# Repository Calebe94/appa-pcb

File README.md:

# Appa keyboard - PCB

This keyboard is inspired by [Plaid](https://github.com/AntonioPelayo/plaid-through-hole-keyboard) and [Gherkin Apls 1.1](https://www.40percent.club/2017/08/gherkin-alps-11.html).

I'm using white APLS switches for this project and Arduino Pro Mini as the core microcontroller.

## Dependencies

* [Kicad 6+](https://packages.debian.org/bookworm/kicad).

## Symbols and Footprints

* I'm using an slightly modded version of [ARDUINO PRO MINI](https://www.snapeda.com/parts/Arduino%20Pro%20Mini/Arduino/view-part/?t=arduino+pro+mini&welcome=home) from [SnapEDA](https://www.snapeda.com). (I've just added a couple of pins at the bottom at the board because my PRO Mini uses the TQFP and QFN/MLF package of the ATMEGA328p);
* For the ALPS switches and the diodes I'm using the [keyboard_parts.pretty](https://github.com/tmk/keyboard_parts.pretty) footprints;
* As for the rest I'm using the KiCAD's stock footprints.

## Schematic

# License

All software is covered under [GNU General Public License v3.0](https://www.gnu.org/licenses/gpl-3.0.en.html).

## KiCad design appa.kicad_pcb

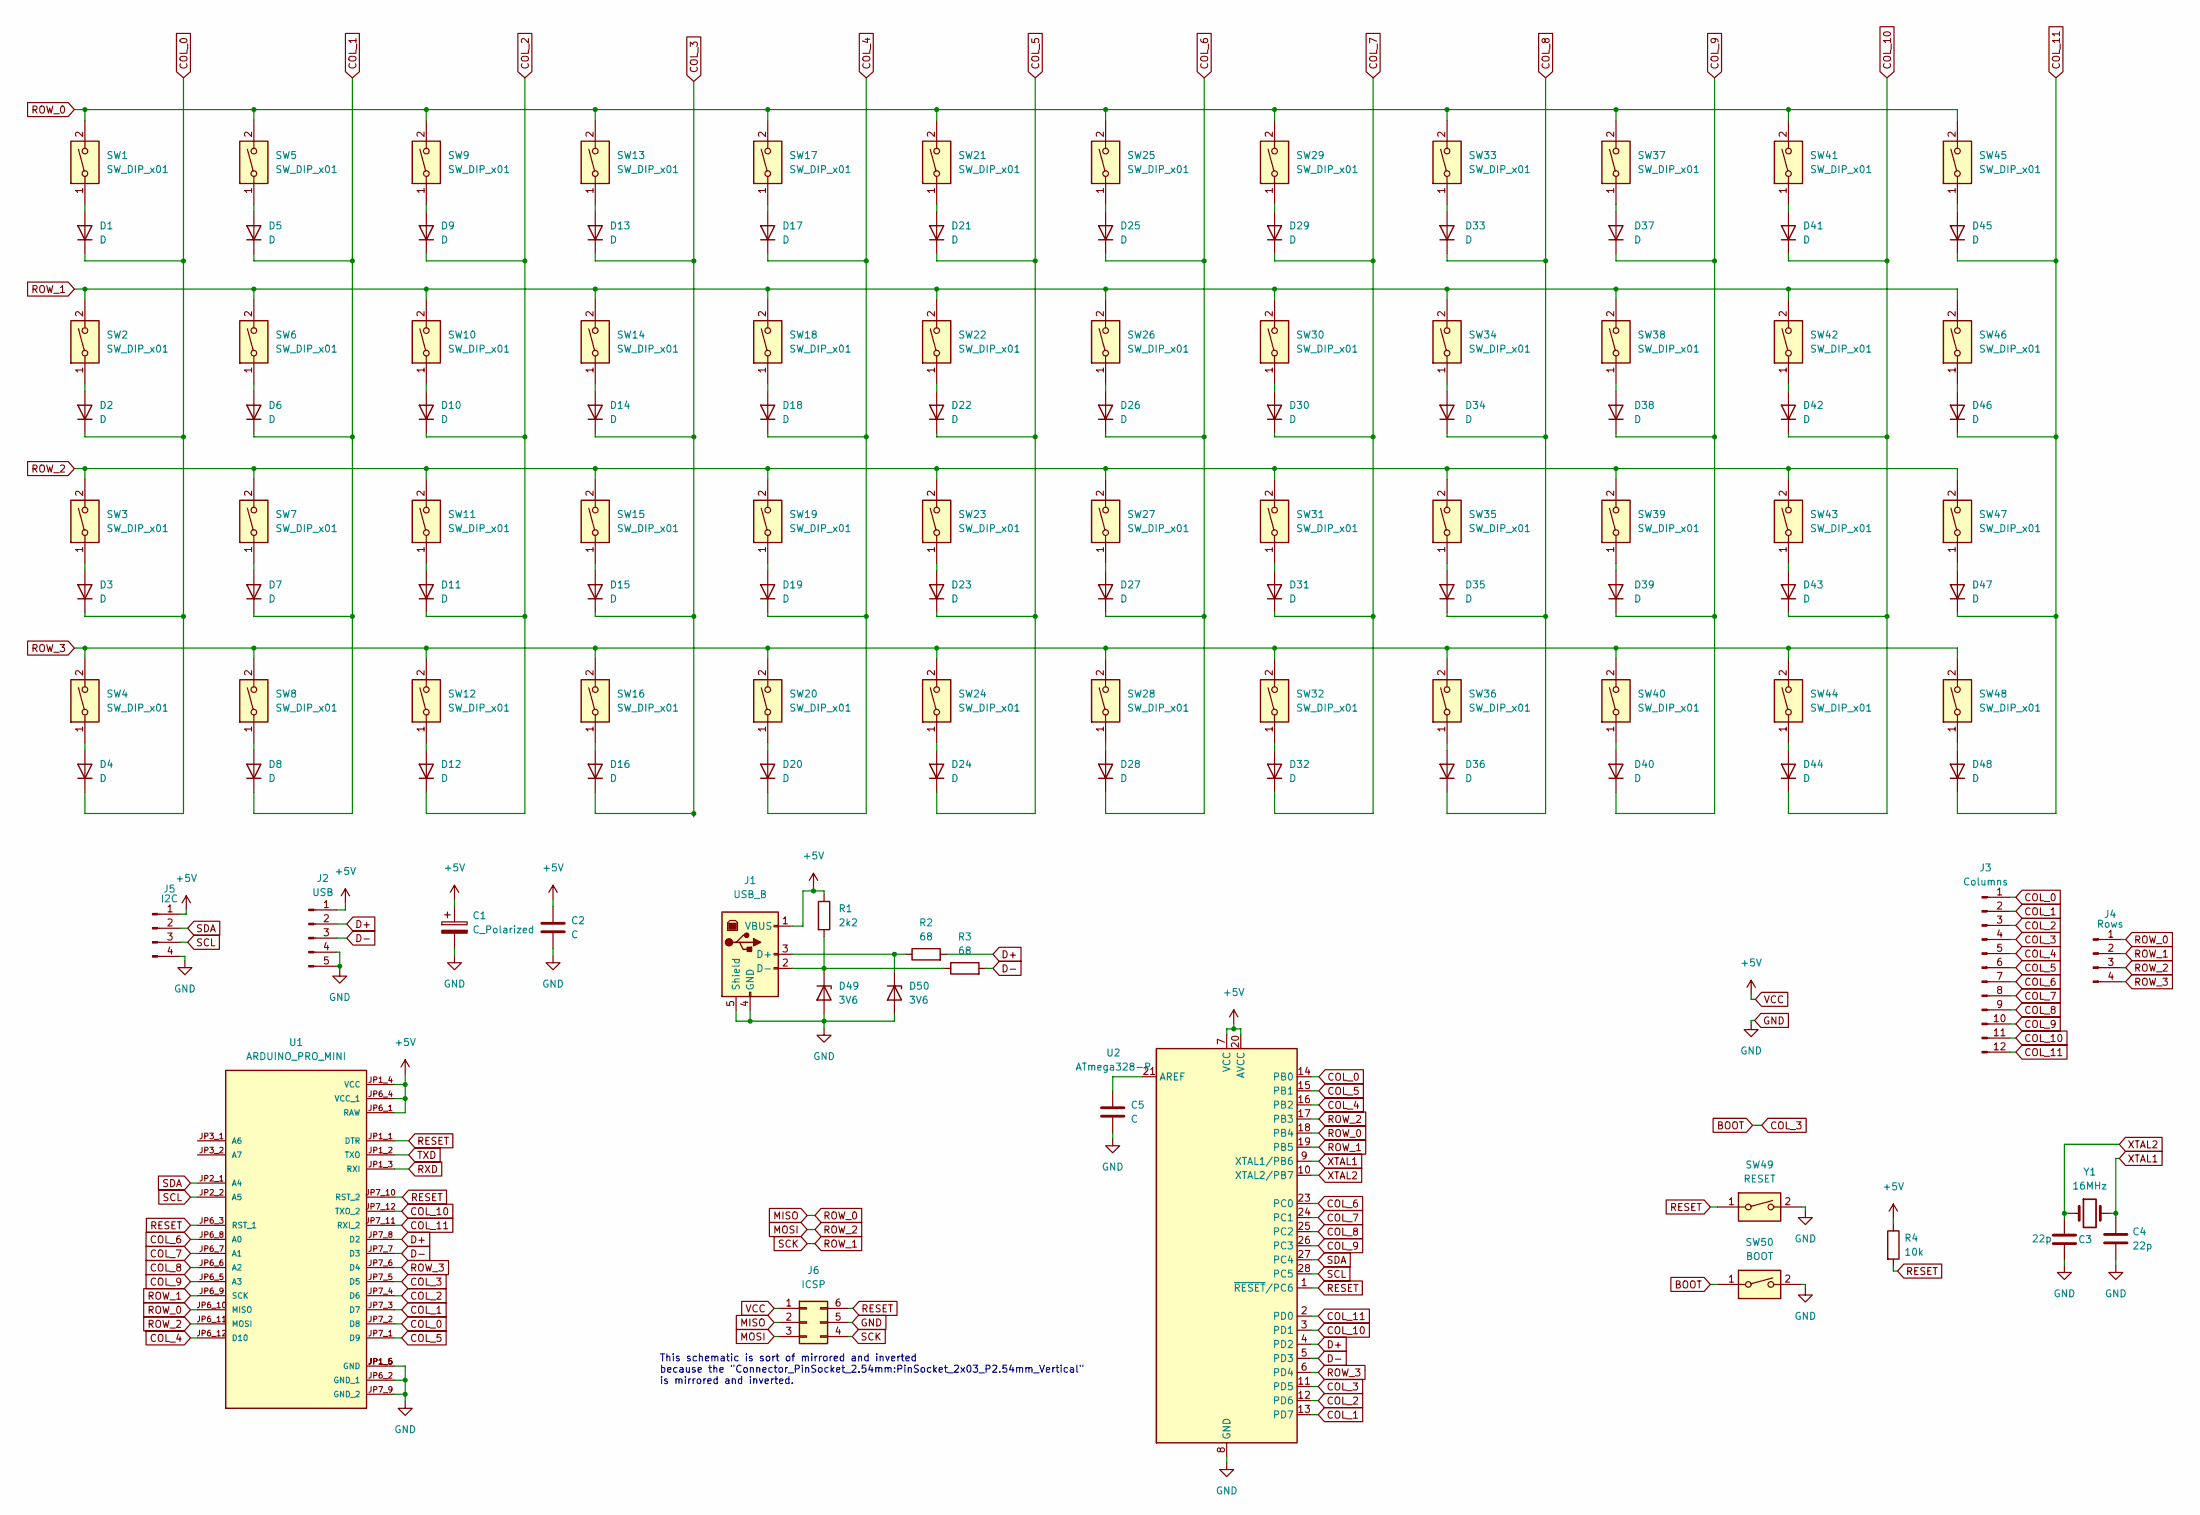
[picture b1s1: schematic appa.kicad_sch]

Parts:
C1: C_Polarized; CP_Radial_D4.0mm_P1.50mm
C2: C; C_Disc_D3.0mm_W1.6mm_P2.50mm
C3, C4: 22p; C_Disc_D3.0mm_W1.6mm_P2.50mm
C5: C; C_Disc_D4.3mm_W1.9mm_P5.00mm
D1, D2, D3, D4, D5, D6, D7, D8, D9, D10, D11, D12, D13, D14, D15, D16, D17, D18, D19, D20, D21, D22, D23, D24, D25, D26, D27, D28, D29, D30, D31, D32, D33, D34, D35, D36, D37, D38, D39, D40, D41, D42, D43, D44, D45, D46, D47, D48: D; D_SOD123_axial
D49, D50: 3V6; D_SOD123_axial
J1: USB_B; USB_B_OST_USB-B1HSxx_Horizontal
J2: USB; PinSocket_1x05_P2.54mm_Vertical
J3: Columns; PinSocket_1x12_P2.54mm_Vertical
J4: Rows; PinSocket_1x04_P2.54mm_Vertical
J5: I2C; PinSocket_1x04_P2.54mm_Vertical
J6: ICSP; PinSocket_2x03_P2.54mm_Vertical
R1: 2k2; R_Axial_DIN0204_L3.6mm_D1.6mm_P7.62mm_Horizontal
R2, R3: 68; R_Axial_DIN0204_L3.6mm_D1.6mm_P7.62mm_Horizontal
R4: 10k; R_Axial_DIN0204_L3.6mm_D1.6mm_P7.62mm_Horizontal
SW1, SW2, SW3, SW4, SW5, SW6, SW7, SW8, SW9, SW10, SW11, SW12, SW13, SW14, SW15, SW16, SW17, SW18, SW19, SW20, SW21, SW22, SW23, SW24, SW25, SW26, SW27, SW28, SW29, SW30, SW31, SW32, SW33, SW34, SW35, SW36, SW37, SW38, SW39, SW40, SW41, SW42, SW43, SW44, SW45, SW46, SW47, SW48: SW_DIP_x01; ALPS_SKCM
SW49: RESET; SW_PUSH_6mm
SW50: BOOT; SW_PUSH_6mm
U1: ARDUINO_PRO_MINI; MODULE_ARDUINO_PRO_MINI; PARTREV N/A
U2: ATmega328-P; DIP-28_W7.62mm
Y1: 16MHz; Crystal_HC18-U_Vertical

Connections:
BOOT: D13.1 (K), D14.1 (K), D15.1 (K), D16.1 (K), J3.4, SW50.1, U1.JP7_5 (D5), U2.11 (PD5)
COL_0: D1.1 (K), D2.1 (K), D3.1 (K), D4.1 (K), J3.1, U1.JP7_2 (D8), U2.14 (PB0)
COL_1: D5.1 (K), D6.1 (K), D7.1 (K), D8.1 (K), J3.2, U1.JP7_3 (D7), U2.13 (PD7)
COL_2: D9.1 (K), D10.1 (K), D11.1 (K), D12.1 (K), J3.3, U1.JP7_4 (D6), U2.12 (PD6)
COL_4: D17.1 (K), D18.1 (K), D19.1 (K), D20.1 (K), J3.5, U1.JP6_12 (D10), U2.16 (PB2)
COL_5: D21.1 (K), D22.1 (K), D23.1 (K), D24.1 (K), J3.6, U1.JP7_1 (D9), U2.15 (PB1)
COL_6: D25.1 (K), D26.1 (K), D27.1 (K), D28.1 (K), J3.7, U1.JP6_8 (A0), U2.23 (PC0)
COL_7: D29.1 (K), D30.1 (K), D31.1 (K), D32.1 (K), J3.8, U1.JP6_7 (A1), U2.24 (PC1)
COL_8: D33.1 (K), D34.1 (K), D35.1 (K), D36.1 (K), J3.9, U1.JP6_6 (A2), U2.25 (PC2)
COL_9: D37.1 (K), D38.1 (K), D39.1 (K), D40.1 (K), J3.10, U1.JP6_5 (A3), U2.26 (PC3)
COL_10: D41.1 (K), D42.1 (K), D43.1 (K), D44.1 (K), J3.11, U1.JP7_12 (TXO_2), U2.3 (PD1)
COL_11: D45.1 (K), D46.1 (K), D47.1 (K), D48.1 (K), J3.12, U1.JP7_11 (RXI_2), U2.2 (PD0)
D+: J2.2, R2.2, U1.JP7_8 (D2), U2.4 (PD2)
D-: J2.3, R3.2, U1.JP7_7 (D3), U2.5 (PD3)
GND: C1.2, C2.2, C3.2, C4.2, C5.2, D49.2 (A), D50.2 (A), J1.4 (GND), J1.5 (Shield), J2.4, J2.5, J5.4, J6.5, SW49.2, SW50.2, U1.JP1_5 (GND), U1.JP1_6 (GND), U1.JP6_2 (GND_1), U1.JP7_9 (GND_2), U2.8 (GND), U2.22 (GND)
MISO: J4.1, J6.2, SW1.2, SW5.2, SW9.2, SW13.2, SW17.2, SW21.2, SW25.2, SW29.2, SW33.2, SW37.2, SW41.2, SW45.2, U1.JP6_10 (MISO), U2.18 (PB4)
MOSI: J4.3, J6.3, SW3.2, SW7.2, SW11.2, SW15.2, SW19.2, SW23.2, SW27.2, SW31.2, SW35.2, SW39.2, SW43.2, SW47.2, U1.JP6_11 (MOSI), U2.17 (PB3)
unnamed: C5.1, U2.21 (AREF)
unnamed: D1.2 (A), SW1.1
unnamed: D2.2 (A), SW2.1
unnamed: D3.2 (A), SW3.1
unnamed: D4.2 (A), SW4.1
unnamed: D5.2 (A), SW5.1
unnamed: D6.2 (A), SW6.1
unnamed: D7.2 (A), SW7.1
unnamed: D8.2 (A), SW8.1
unnamed: D9.2 (A), SW9.1
unnamed: D10.2 (A), SW10.1
unnamed: D11.2 (A), SW11.1
unnamed: D12.2 (A), SW12.1
unnamed: D13.2 (A), SW13.1
unnamed: D14.2 (A), SW14.1
unnamed: D15.2 (A), SW15.1
unnamed: D16.2 (A), SW16.1
unnamed: D17.2 (A), SW17.1
unnamed: D18.2 (A), SW18.1
unnamed: D19.2 (A), SW19.1
unnamed: D20.2 (A), SW20.1
unnamed: D21.2 (A), SW21.1
unnamed: D22.2 (A), SW22.1
unnamed: D23.2 (A), SW23.1
unnamed: D24.2 (A), SW24.1
unnamed: D25.2 (A), SW25.1
unnamed: D26.2 (A), SW26.1
unnamed: D27.2 (A), SW27.1
unnamed: D28.2 (A), SW28.1
unnamed: D29.2 (A), SW29.1
unnamed: D30.2 (A), SW30.1
unnamed: D31.2 (A), SW31.1
unnamed: D32.2 (A), SW32.1
unnamed: D33.2 (A), SW33.1
unnamed: D34.2 (A), SW34.1
unnamed: D35.2 (A), SW35.1
unnamed: D36.2 (A), SW36.1
unnamed: D37.2 (A), SW37.1
unnamed: D38.2 (A), SW38.1
unnamed: D39.2 (A), SW39.1
unnamed: D40.2 (A), SW40.1
unnamed: D41.2 (A), SW41.1
unnamed: D42.2 (A), SW42.1
unnamed: D43.2 (A), SW43.1
unnamed: D44.2 (A), SW44.1
unnamed: D45.2 (A), SW45.1
unnamed: D46.2 (A), SW46.1
unnamed: D47.2 (A), SW47.1
unnamed: D48.2 (A), SW48.1
unnamed: D49.1 (K), J1.2 (D-), R1.2, R3.1
unnamed: D50.1 (K), J1.3 (D+), R2.1
RESET: J6.6, R4.2, SW49.1, U1.JP1_1 (DTR), U1.JP6_3 (RST_1), U1.JP7_10 (RST_2), U2.1 (~RESET/PC6)
ROW_1: J4.2, J6.4, SW2.2, SW6.2, SW10.2, SW14.2, SW18.2, SW22.2, SW26.2, SW30.2, SW34.2, SW38.2, SW42.2, SW46.2, U1.JP6_9 (SCK), U2.19 (PB5)
ROW_3: J4.4, SW4.2, SW8.2, SW12.2, SW16.2, SW20.2, SW24.2, SW28.2, SW32.2, SW36.2, SW40.2, SW44.2, SW48.2, U1.JP7_6 (D4), U2.6 (PD4)
RXD: U1.JP1_3 (RXI)
SCL: J5.3, U1.JP2_2 (A5), U2.28 (PC5)
SDA: J5.2, U1.JP2_1 (A4), U2.27 (PC4)
TXD: U1.JP1_2 (TXO)
VCC: C1.1, C2.1, J1.1 (VBUS), J2.1, J5.1, J6.1, R1.1, R4.1, U1.JP1_4 (VCC), U1.JP6_1 (RAW), U1.JP6_4 (VCC_1), U2.7 (VCC), U2.20 (AVCC)
XTAL1: C4.1, U2.9 (XTAL1/PB6), Y1.2
XTAL2: C3.1, U2.10 (XTAL2/PB7), Y1.1

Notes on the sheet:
This schematic is sort of mirrored and inverted because the "Connector_PinSocket_2.54mm:PinSocket_2x03_P2.54mm_Vertical" is mirrored and inverted.

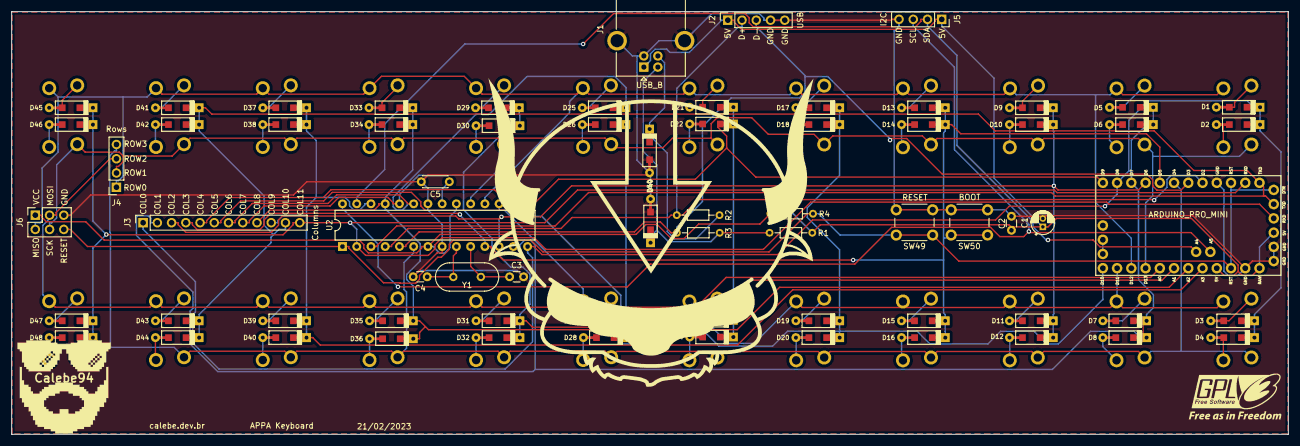
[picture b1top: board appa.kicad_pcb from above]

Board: 2 copper layers, 227.8 x 75.4 mm, 120 parts (0 on the bottom side), 76 nets.

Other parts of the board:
Calebe94: Calebe94; calebe94
G1: LOGO; gpl3

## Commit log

2022-10-25 Changed routes
2022-10-26 Added appa and my logo as silk
2022-10-26 Changed switches layout to be read from left to right
2022-10-27 Added license file
2022-10-27 Added schematic and updated readme
2022-10-27 Added changelog file
2022-10-28 Added gpl3 logo silk
2022-10-28 Added atmega328 standalone schematic
2022-10-28 Added gerber folder
2022-11-09 Added BOM
2022-11-09 Added my logo
2022-11-16 Added gpl3 logo
2022-11-16 Added fp info cache
2022-12-07 Added .gitignore file
2022-12-07 Updated README
    - Renamed project;
    - Changed schematic image to `.jpeg`;
    - Added keyboard picture.
2022-12-07 Removed BOM file
2022-12-07 Renamed project to appa
2023-02-21 Added github templates
2023-02-21 Removed links from tinytoolsh project
2023-02-21 Moved code of conduct and contributing files to root project folder
2023-02-22 Fixed unwired pins
2023-02-22 Removed gerber folder
2023-02-22 Updated changelog with 1.1.0 changes
